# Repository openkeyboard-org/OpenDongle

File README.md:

# OpenDongle

OpenDongle is an open-source keyboard dongle project.

## Repository layout

- `firmware/` — firmware source and related software artifacts.
- `hardware/` — hardware design files and documentation.
- `tools/` — development and support tooling.

## Licensing

- Firmware and tools software: [Apache License 2.0](./firmware/LICENSE).
- Hardware designs: [CERN Open Hardware Licence Version 2 - Weakly Reciprocal](./hardware/LICENSE).
- Third-party firmware provenance is recorded in [firmware/NOTICE](./firmware/NOTICE),
  and the independently created antenna design's provenance is recorded in
  [hardware/NOTICE](./hardware/NOTICE).

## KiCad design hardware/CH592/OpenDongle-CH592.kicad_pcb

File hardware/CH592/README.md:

# OpenDongle CH592

OpenDongle CH592 is a compact USB Type-A 2.4 GHz receiver built around the WCH CH592D RISC-V wireless MCU. The PCB is 16.35 mm x 9.90 mm and uses a PCB-edge USB connector and an independently created, WCH-informed 2.4 GHz PCB antenna.

Unlike the [CH570](../CH570/) implementation, which runs the MCU straight from VBUS on its internal regulator, the CH592 is powered from a 3.3 V LDO.

## Design files

| File or directory | Purpose |
| --- | --- |
| `OpenDongle-CH592.kicad_pro` | KiCad 10 project and design-rule settings |
| `OpenDongle-CH592.kicad_sch` | Schematic |
| `OpenDongle-CH592.kicad_pcb` | PCB layout |
| `lib/OpenDongle.kicad_sym` | Project-owned CH592D and four-pin PCB USB symbols |
| `lib/OpenDongle.pretty/` | Project-owned USB edge connector and independently created, WCH-informed antenna footprints |
| `sym-lib-table`, `fp-lib-table` | Portable project-local library configuration |
| `fab/` | Exported outputs: schematic PDF and gerber/NC drill set (see [Fabrication outputs](#fabrication-outputs)) |

Open the project with KiCad 10 or later. The library tables use `${KIPRJMOD}` paths, so the project resolves every symbol and footprint from this directory and does not depend on global KiCad configuration. Nothing needs to be added to your global symbol or footprint library tables.

## Electrical design notes

- USB VBUS (5 V) feeds U2, an XC6206P332MR-G LDO, whose 3.3 V output supplies the CH592D VIO33/VDD33 pin (pin 5). C1 (1 uF) is the LDO input capacitor and C2 (1 uF) is its output capacitor.
- Y1 is a 32 MHz crystal on X32MI/X32MO (pins 13 and 12). No external load capacitors are fitted; the design relies on the CH592 programmable internal crystal load capacitance.
- The RF output (ANT, pin 15) connects directly to the independently created, WCH-informed PCB antenna.
- USB data connects to the CH592D native USB pins: D+ to PB11/UD+ (pin 10) and D- to PB10/UD- (pin 11).
- GND reaches the CH592D through the exposed pad (pin 21).
- The nine unused GPIOs (pins 1, 2, 7, 8, 9, 17, 18, 19, 20) carry no-connect flags.
- AE2 and J1 represent copper footprints fabricated as part of the PCB. They are excluded from the assembly BOM and position file at both the symbol level (`in_bom no`, `in_pos_files no`) and the footprint level (`exclude_from_bom`, `exclude_from_pos_files`), so they do not appear in the Fabrication Toolkit output as unsourceable line items.

### The internal DC-DC is deliberately not used

Two parts of this schematic look like mistakes and are not. **Do not "fix" them.**

**VSW (pin 4) is tied directly to VDCID (pin 3), with VDCIA (pin 16) on the same net, and there is no inductor on the board.** This is the configuration the datasheet specifies when the DC-DC converter is disabled.

VSW is the internal power path from VDD33 when the DC-DC is bypassed, so it must **not** be left floating. The decoupling values follow the datasheet's DC-DC-disabled recommendations:

| Pin | Datasheet, DC-DC disabled | This design |
| --- | --- | --- |
| VDCID (3) | "0.1uF or more" | C4, 1 uF |
| VINTA (14) | "0.47uF is recommended" | C5, 470 nF |
| VDD33 (5) | "1uF is recommended" | C2, 1 uF |

The DC-DC is off by default at power-on and is simply never enabled in firmware. WCH's own CH592F reference designs use the *other* branch of this note (a 10 uH inductor from VSW to VDCID), which is why they look different.

### PB15 (pin 6) is tied to GND on purpose

**PB15/TCK/MISO_/SCL is a boot strap, not a stray ground.** Holding it low forces a unflashed part to come up in ISP mode so it can be programmed over USB. The first programming pass flashes the firmware *and* moves the boot source to the alternate boot pin, which is shared with the USB line; after that, the ground on PB15 is inert.

This also gives the board a recovery path: a fully erased part falls back to the PB15 strap and always re-enters ISP.

Consequences to keep in mind:

- Firmware must never configure PB15 as a push-pull output. Driving it high would short it to ground.
- PB15 is also TCK, so the two-wire debug interface is not usable while the strap is fitted.

This strap is the sole remaining ERC warning; see [Design verification](#design-verification) below.

See the [WCH CH592 datasheet](https://github.com/openwch/ch592/blob/main/Datasheet/CH592DS1_EN.PDF) for the power, oscillator, RF, USB, and package requirements.

## Design verification

```sh
kicad-cli sch erc --severity-all OpenDongle-CH592.kicad_sch     # 0 errors, 1 expected warning
kicad-cli pcb drc --severity-all --schematic-parity OpenDongle-CH592.kicad_pcb   # 0 violations, 0 parity issues
```

The single ERC warning is expected and understood:

```
[pin_to_pin]: Pins of type Bidirectional and Power output are connected
    Symbol U3 Pin 6 [PB15/TCK/MISO_/SCL, Bidirectional]
    Symbol #FLG02 Pin 1 [Power output]
```

This is the PB15 boot strap sitting on the GND net, described above. It is not a defect. Fitting the pull-down resistor proposed under [Known issues](#known-issues-and-next-revision) removes PB15 from the GND net and clears the warning.

## Fabrication outputs

`fab/` holds the exported outputs: the schematic as PDF, and the gerber/NC
drill set under `fab/gerbers/`. The KiCad sources remain the design of
record — regenerate the exports with KiCad 10 whenever the schematic or
layout changes:

```sh
kicad-cli sch export pdf -o fab/OpenDongle-CH592-schematic.pdf OpenDongle-CH592.kicad_sch
kicad-cli pcb export gerbers -o fab/gerbers/ \
    -l F.Cu,B.Cu,F.Paste,B.Paste,F.Silkscreen,B.Silkscreen,F.Mask,B.Mask,Edge.Cuts \
    --no-protel-ext --check-zones OpenDongle-CH592.kicad_pcb
kicad-cli pcb export drill -o fab/gerbers/ --excellon-separate-th \
    --generate-map --map-format gerberx2 OpenDongle-CH592.kicad_pcb
```

Anyone ordering from these files must still pass the stackup and antenna
requirements below to the fabricator; the gerbers alone do not carry them.
(JLC-oriented assembly outputs from the Fabrication Toolkit plugin go to
`production/`, which stays untracked.)

## Fabrication requirements

The antenna geometry and USB connector make the board construction part of the electrical and mechanical design. Use these settings unless a revised PCB has been validated:

| Parameter | Requirement |
| --- | --- |
| Layer count | 2 copper layers |
| Finished board size | 16.35 mm x 9.90 mm |
| Finished thickness | 0.8 mm nominal (35 um + 0.73 mm core + 35 um) |
| Material | FR-4 |
| Copper | 1 oz / 35 um outer copper |
| Surface finish | ENIG recommended; hard gold on the USB contacts is preferred for high insertion-cycle production |
| Minimum finished drill | 0.20 mm |
| Minimum track/space used | 0.15 mm track, 0.127 mm design-rule clearance minimum |
| Soldermask | Both sides; no soldermask over the USB contacts or antenna conductor |

Additional requirements and checks:

1. Preserve the antenna copper, ground keepout, board thickness, and via fence exactly. The antenna is designed for 0.8 mm FR-4; a different thickness detunes it. Do not allow the fabricator to add serial numbers, tooling features, or anything else in the antenna region.
2. Keep the board outline and USB contact geometry at 1:1 scale. If an edge bevel is requested, confirm that the fabricator supports it on a 0.8 mm board without shortening or damaging the USB contacts.
3. Verify the board USB contact fits in several Type-A receptacles before a production run.
4. The enclosure and carrier must not place metal or conductive material over the antenna region.

## USB receiver shell

This board is 0.05 mm narrower and 0.1 mm shorter than the CH570, so the same [USB receiver shell](https://item.taobao.com/item.htm?id=1042083494471) that was verified against the CH570 is the intended enclosure. Its fit has been verified on the CH570 but not yet on this board. Other shells designed for the same PCB dimensions and specification should also work.

## Suggested BOM

The listed LCSC/JLCPCB numbers are suggested assembly parts, not sole-source requirements. Substitutes should match the value, package, dielectric/tolerance, voltage rating, and crystal parameters.

| References | Qty | Value / part | Package | Suggested LCSC part | Notes |
| --- | ---: | --- | --- | --- | --- |
| U3 | 1 | WCH CH592D | QFN-20, 3 mm x 3 mm, exposed pad | C41417128 | Confirm pin-1 orientation and exposed-pad soldering |
| U2 | 1 | XC6206P332MR-G, 3.3 V LDO | SOT-23-3 | C5446 | |
| Y1 | 1 | 32 MHz crystal | 3225, 4 pad | C7294588 | No external load capacitors fitted; confirm the part's load capacitance matches what firmware programs into the internal load caps |
| C1, C2, C4 | 3 | 1 uF | 0603 | C15849 | X5R or better, 10 V minimum |
| C5 | 1 | 470 nF | 0603 | C47339 | Alternate: C1623 |

AE2 (PCB antenna) and J1 (PCB USB connector) are fabricated as PCB copper and are not assembly parts.

## Known issues and next revision

Neither of these prevents the current board from being built, but both should be addressed in the next spin.

### Strap PB15 through a 4.7 kOhm pull-down

The strap is currently a direct connection to GND. Fitting a resistor between PB15 and GND instead would preserve the ISP behaviour while removing the short if firmware ever drives the pin high.

**Use 4.7 kOhm, 0603, 1% (suggested LCSC C23162).** The boot ROM's internal pull-up sources up to 90 uA (IUP max, datasheet Table 20-2) and VIL is 0.9 V max, so:

| Pull-down | Worst-case V(PB15) | Margin to VIL | Current if driven high |
| --- | --- | --- | --- |
| 10 kOhm | 0.90 V | **none - exactly at the limit** | 0.33 mA |
| **4.7 kOhm** | **0.42 V** | **2.1x** | **0.70 mA** |
| 3.3 kOhm | 0.30 V | 3.0x | 1.0 mA |

Adopting this also clears the remaining ERC warning, because PB15 leaves the GND net. The cost is placement: the 0603 has to fit near U3 pin 6 without intruding on the antenna keepout, on an already tight board.

### Close the reference designator gaps

The designators are non-contiguous: there is no **C3** and no **U1** (the parts jump from U2 to U3). This is cosmetic, but it makes the BOM harder to review and invites the question of whether a part was lost. Renumber on the next spin.

## Source attribution

- The 0.8 mm FR-4 antenna was independently created, informed by the WCH reference antenna published in the [openwch schematic/PCB library](https://github.com/openwch/schpcb_lib); no WCH CAD or artwork file was copied, imported, converted, or traced.
- The PCB USB connector footprint is derived from the [USB armory](https://github.com/usbarmory/usbarmory) hardware design.

## License

This hardware design, including the independently created antenna
implementation described in [`../NOTICE`](../NOTICE), is licensed under the
CERN Open Hardware Licence Version 2 - Weakly Reciprocal. See
[`LICENSE`](LICENSE).

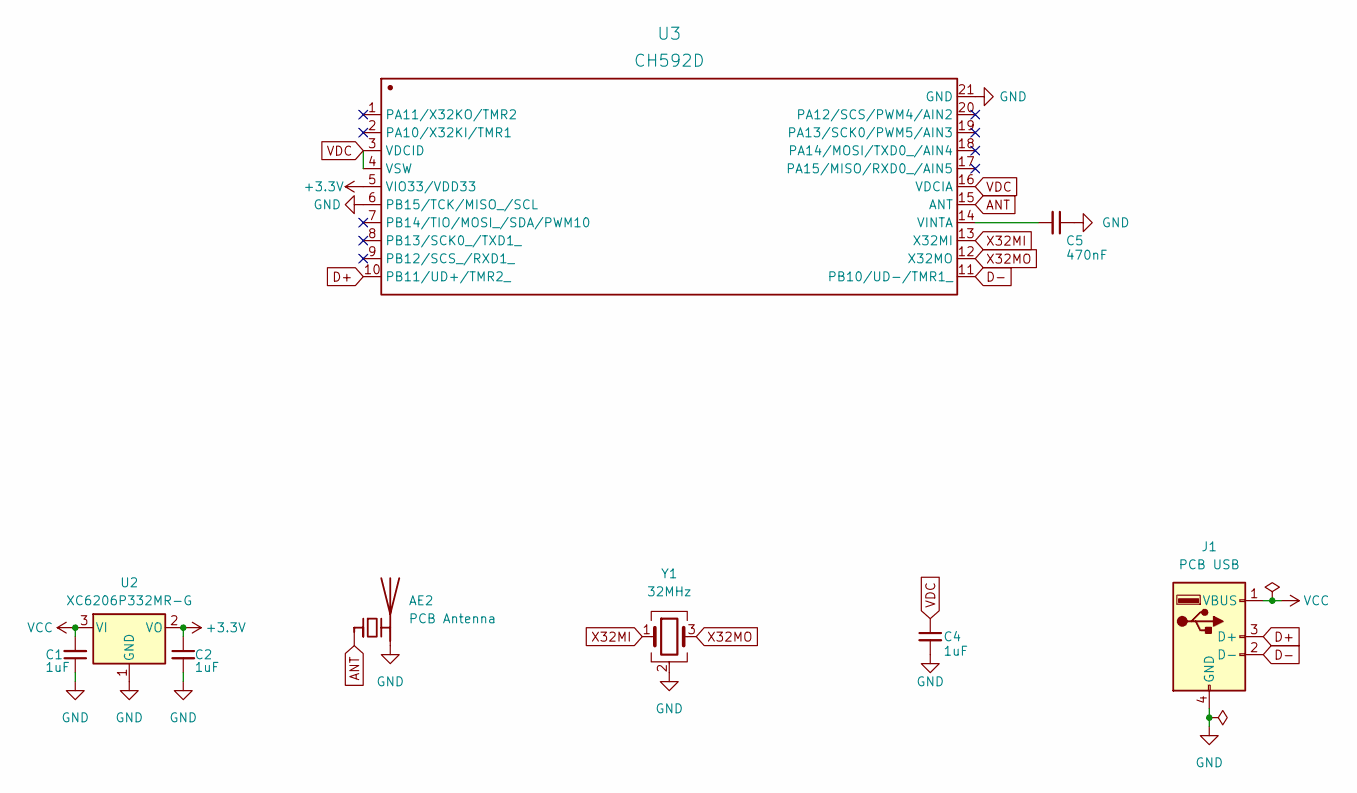
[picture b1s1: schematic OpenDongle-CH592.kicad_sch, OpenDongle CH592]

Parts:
AE2: PCB Antenna; ANT-F-2-2.4G-0.8MM-FR4-WCH
C1, C2, C4: 1uF; C_0603_1608Metric; LCSC C15849
C5: 470nF; C_0603_1608Metric; LCSC C47339
J1: PCB USB; usb-PCB
U2: XC6206P332MR-G; SOT-23-3; LCSC C5446
U3: CH592D; QFN-20-1EP_3x3mm_P0.4mm_EP1.65x1.65mm; Manufacturer Part CH592D; LCSC Part C41417128
Y1: 32MHz; Crystal_SMD_3225-4Pin_3.2x2.5mm; LCSC C7294588

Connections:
+3.3V: C2.1, U2.2 (VO), U3.5 (VIO33/VDD33)
ANT: AE2.1 (FEED), U3.15 (ANT)
D+: J1.3 (D+), U3.10 (PB11/UD+/TMR2_)
D-: J1.2 (D-), U3.11 (PB10/UD-/TMR1_)
GND: AE2.2 (PCB_Trace), C1.1, C2.2, C4.2, C5.1, J1.4 (GND), U2.1 (GND), U3.6 (PB15/TCK/MISO_/SCL), U3.21 (GND), Y1.2 (G), Y1.4 (G)
unnamed: C5.2, U3.14 (VINTA)
VCC: C1.2, J1.1 (VBUS), U2.3 (VI)
VDC: C4.1, U3.3 (VDCID), U3.4 (VSW), U3.16 (VDCIA)
X32MI: U3.13 (X32MI), Y1.1
X32MO: U3.12 (X32MO), Y1.3

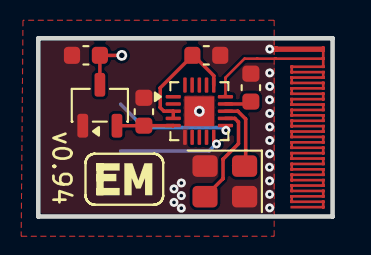
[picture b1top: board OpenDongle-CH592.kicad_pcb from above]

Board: 2 copper layers, 16.3 x 9.9 mm, 9 parts (1 on the bottom side), 10 nets.

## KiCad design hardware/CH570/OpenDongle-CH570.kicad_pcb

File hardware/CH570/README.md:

# OpenDongle CH570

OpenDongle CH570 is a compact USB Type-A 2.4 GHz receiver built around the WCH CH570Q RISC-V wireless MCU. The PCB is 16.4 mm x 10.0 mm and uses a PCB-edge USB connector and an independently created, WCH-informed 2.4 GHz PCB antenna.

## Design files

| File or directory | Purpose |
| --- | --- |
| `OpenDongle-CH570.kicad_pro` | KiCad 10 project and design-rule settings |
| `OpenDongle-CH570.kicad_sch` | Schematic |
| `OpenDongle-CH570.kicad_pcb` | PCB layout |
| `lib/OpenDongle.kicad_sym` | Project-owned CH570Q and four-pin PCB USB symbols |
| `lib/OpenDongle.pretty/` | Project-owned USB edge connector and independently created, WCH-informed antenna footprints |
| `sym-lib-table`, `fp-lib-table` | Portable project-local library configuration |
| `fab/` | Exported outputs: schematic PDF and gerber/NC drill set (see [Fabrication outputs](#fabrication-outputs)) |

Open the project with KiCad 10 or later. The library tables use `${KIPRJMOD}` paths, so the project resolves every symbol and footprint from this directory and does not depend on global KiCad configuration. Nothing needs to be added to your global symbol or footprint library tables.

## Electrical design notes

- USB VBUS supplies the CH570Q V5 pin (pin 2) directly. There is no external regulator; the CH570 regulates 3.3 V internally.
- R1 is the 1.5 kOhm connection required by WCH between V5 and the internally regulated VDD33/VIO33 rail (pin 1) for direct 5 V operation.
- Both V5 and VDD33/VIO33 have 2.2 uF bulk and 100 nF high-frequency decoupling: C1/C2 on V5, C3/C4 on VDD33.
- Y1 is a 32 MHz, 8 pF-load crystal on XI/XO (pins 9 and 8). The CH570 provides programmable internal crystal load capacitance, so external load capacitors are not fitted.
- The RF output (ANT, pin 10) connects directly to the independently created, WCH-informed PCB antenna, as recommended by the CH570 datasheet.
- USB data connects to the CH570Q native USB pins: D+ to PA1/UDP (pin 4) and D- to PA0/UDM (pin 3).
- GND reaches the CH570Q through the exposed pad (pin 11).
- The three unused GPIOs (pins 5, 6, 7) carry no-connect flags.
- AE2 and J1 represent copper footprints fabricated as part of the PCB. They are excluded from the assembly BOM and position file at both the symbol level (`in_bom no`, `in_pos_files no`) and the footprint level (`exclude_from_bom`, `exclude_from_pos_files`), so they do not appear in the Fabrication Toolkit output as unsourceable line items.

See the [WCH CH572/CH570 datasheet](https://www.wch-ic.com/downloads/CH572DS1_PDF.html) for the power, oscillator, RF, USB, and package requirements.

## Design verification

This design passes both checks cleanly with KiCad 10:

```sh
kicad-cli sch erc --severity-all OpenDongle-CH570.kicad_sch     # 0 errors, 0 warnings
kicad-cli pcb drc --severity-all --schematic-parity OpenDongle-CH570.kicad_pcb   # 0 violations, 0 parity issues
```

## Fabrication outputs

`fab/` holds the exported outputs: the schematic as PDF, and the gerber/NC
drill set under `fab/gerbers/`. The KiCad sources remain the design of
record — regenerate the exports with KiCad 10 whenever the schematic or
layout changes:

```sh
kicad-cli sch export pdf -o fab/OpenDongle-CH570-schematic.pdf OpenDongle-CH570.kicad_sch
kicad-cli pcb export gerbers -o fab/gerbers/ \
    -l F.Cu,B.Cu,F.Paste,B.Paste,F.Silkscreen,B.Silkscreen,F.Mask,B.Mask,Edge.Cuts \
    --no-protel-ext --check-zones OpenDongle-CH570.kicad_pcb
kicad-cli pcb export drill -o fab/gerbers/ --excellon-separate-th \
    --generate-map --map-format gerberx2 OpenDongle-CH570.kicad_pcb
```

Anyone ordering from these files must still pass the stackup and antenna
requirements below to the fabricator; the gerbers alone do not carry them.
(JLC-oriented assembly outputs from the Fabrication Toolkit plugin go to
`production/`, which stays untracked.)

## Fabrication requirements

The antenna geometry and USB connector make the board construction part of the electrical and mechanical design. Use these settings unless a revised PCB has been validated:

| Parameter | Requirement |
| --- | --- |
| Layer count | 2 copper layers |
| Finished board size | 16.4 mm x 10.0 mm |
| Finished thickness | 0.8 mm nominal (35 um + 0.73 mm core + 35 um) |
| Material | FR-4 |
| Copper | 1 oz / 35 um outer copper |
| Surface finish | ENIG recommended; hard gold on the USB contacts is preferred for high insertion-cycle production |
| Minimum finished drill | 0.20 mm |
| Minimum track/space used | 0.15 mm track, 0.127 mm design-rule clearance minimum |
| Soldermask | Both sides; no soldermask over the USB contacts or antenna conductor |

Additional requirements and checks:

1. Preserve the antenna copper, ground keepout, board thickness, and via fence exactly. The antenna is designed for 0.8 mm FR-4; a different thickness detunes it. Do not allow the fabricator to add serial numbers, tooling features, or anything else in the antenna region.
2. Keep the board outline and USB contact geometry at 1:1 scale. If an edge bevel is requested, confirm that the fabricator supports it on a 0.8 mm board without shortening or damaging the USB contacts.
3. Verify the board USB contact fits in several Type-A receptacles before a production run.
4. The enclosure and carrier must not place metal or conductive material over the antenna region.

## USB receiver shell

This [USB receiver shell](https://item.taobao.com/item.htm?id=1042083494471) has been verified to fit and work well with the PCB. Other shells designed for the same PCB dimensions and specification should also work, but their fit has not been verified.

## Suggested BOM

The listed LCSC/JLCPCB numbers are suggested assembly parts, not sole-source requirements. Substitutes should match the value, package, dielectric/tolerance, voltage rating, and crystal parameters.

| References | Qty | Value / part | Package | Suggested LCSC part | Notes |
| --- | ---: | --- | --- | --- | --- |
| U1 | 1 | WCH CH570Q | DFN-10, 3 mm x 3 mm, exposed pad | C49260680 | Confirm pin-1 orientation and exposed-pad soldering |
| Y1 | 1 | 32 MHz crystal | 2016, 4 pad | C37635332 | 8 pF load, +/-10 ppm tolerance, 40 ohm maximum ESR |
| R1 | 1 | 1.5 kOhm, 1% | 0603 | C22843 | Required V5-to-VDD33 connection |
| C1, C3 | 2 | 2.2 uF | 0603 | C23630 | X5R or better, 10 V minimum; suggested part is 16 V |
| C2, C4 | 2 | 100 nF | 0603 | C14663 | X7R or better, 10 V minimum |

AE2 (PCB antenna) and J1 (PCB USB connector) are fabricated as PCB copper and are not assembly parts.

## Source attribution

- The 0.8 mm FR-4 antenna was independently created, informed by the WCH reference antenna published in the [openwch schematic/PCB library](https://github.com/openwch/schpcb_lib); no WCH CAD or artwork file was copied, imported, converted, or traced.
- The PCB USB connector footprint is derived from the [USB armory](https://github.com/usbarmory/usbarmory) hardware design.

## License

This hardware design, including the independently created antenna
implementation described in [`../NOTICE`](../NOTICE), is licensed under the
CERN Open Hardware Licence Version 2 - Weakly Reciprocal. See
[`LICENSE`](LICENSE).

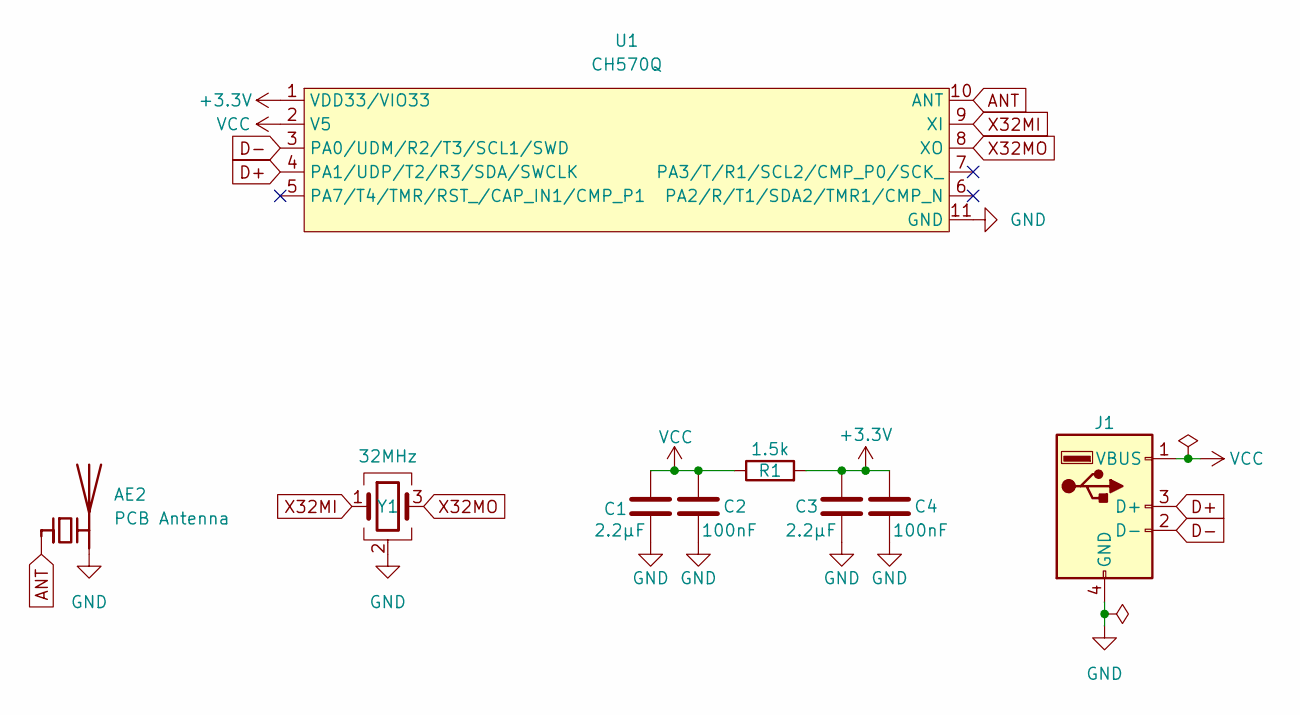
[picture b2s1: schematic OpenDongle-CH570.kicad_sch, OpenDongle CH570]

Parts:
AE2: PCB Antenna; ANT-F-2-2.4G-0.8MM-FR4-WCH
C1, C3: 2.2µF; C_0603_1608Metric; LCSC C23630
C2, C4: 100nF; C_0603_1608Metric; LCSC C14663
J1: PCB USB; usb-PCB
R1: 1.5k; R_0603_1608Metric; LCSC C22843
U1: CH570Q; DFN-10-1EP_3x3mm_P0.5mm_EP1.7x2.5mm; LCSC C49260680
Y1: 32MHz; Crystal_SMD_2016-4Pin_2.0x1.6mm; LCSC C37635332

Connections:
+3.3V: C3.1, C4.1, R1.2, U1.1 (VDD33/VIO33)
ANT: AE2.1 (FEED), U1.10 (ANT)
D+: J1.3 (D+), U1.4 (PA1/UDP/T2/R3/SDA/SWCLK)
D-: J1.2 (D-), U1.3 (PA0/UDM/R2/T3/SCL1/SWD)
GND: AE2.2 (PCB_Trace), C1.2, C2.2, C3.2, C4.2, J1.4 (GND), U1.11 (GND), Y1.2 (G), Y1.4 (G)
VCC: C1.1, C2.1, J1.1 (VBUS), R1.1, U1.2 (V5)
X32MI: U1.9 (XI), Y1.1
X32MO: U1.8 (XO), Y1.3

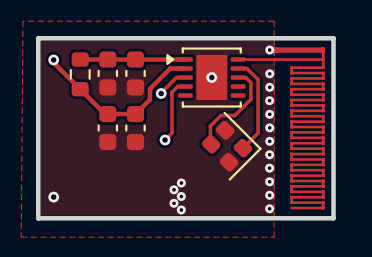
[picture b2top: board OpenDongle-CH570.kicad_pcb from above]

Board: 2 copper layers, 16.4 x 10.0 mm, 9 parts (1 on the bottom side), 8 nets.

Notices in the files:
hardware/CH570/OpenDongle-CH570.kicad_sch:
Copyright 2026 Eric Molitor (EMulator)
CERN-OHL-W CERN Open Hardware Licence Version 2 - Weakly Reciprocal
hardware/CH590/OpenDongle-CH592.kicad_sch:
CERN-OHL-S CERN Open Hardware Licence Version 2 - Strong-Reciprocal
